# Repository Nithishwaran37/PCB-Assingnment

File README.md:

View this project on [CADLAB.io](https://cadlab.io/project/29285). 

# PCB-Assingnment

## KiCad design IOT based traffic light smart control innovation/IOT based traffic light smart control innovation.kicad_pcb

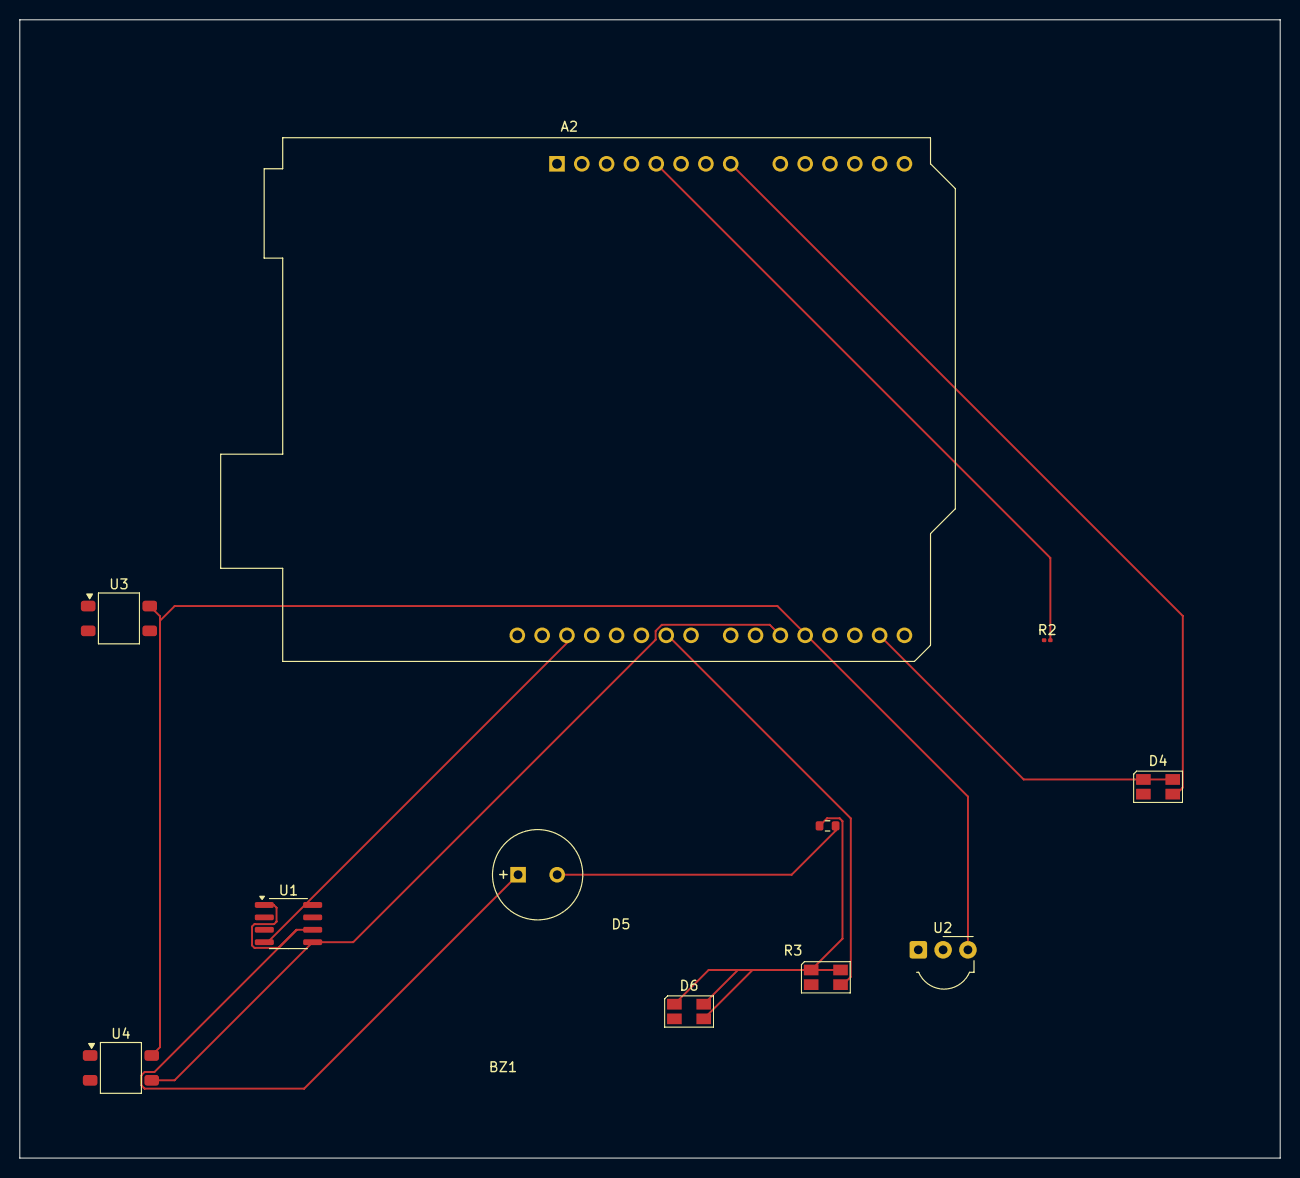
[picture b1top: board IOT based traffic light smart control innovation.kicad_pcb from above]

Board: 2 copper layers, 129.0 x 116.5 mm, 11 parts (0 on the bottom side), 10 nets.

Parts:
A2: Arduino_UNO_R2
BZ1: Buzzer; MagneticBuzzer_PUI_AT-0927-TT-6-R
D4, D5, D6: ASMB-MTB1-0A3A2; LED_Avago_PLCC4_3.2x2.8mm_CW
R2: R; R_0201_0603Metric
R3: R_Small_US; R_0603_1608Metric
U1: ESP-PSRAM32; SOIC-8_3.9x4.9mm_P1.27mm
U2: TSDP341xx; Vishay_MOLD-3Pin
U3, U4: IRM-H6xxT; Everlight_IRM-H6xxT

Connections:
Earth: BZ1.2 (-), R3.2
unnamed: A2.5 (+5V), R2.2
unnamed: A2.16 (D1/TX), D4.1 (RK), D4.2 (GK)
unnamed: A2.19 (D4), U2.3 (Vs), U3.4 (Vcc), U4.4 (Vcc)
unnamed: A2.20 (D5), U1.5 (SI/SIO), U4.3 (OUT)
unnamed: A2.24 (D9), D5.3 (BK)
unnamed: A2.28 (D13), U1.4 (VSS), U1.8 (VCC)
unnamed: A2.8 (VIN), D4.3 (BK)
unnamed: BZ1.1 (+), U1.1 (~CE), U1.6 (SCLK)
unnamed: D5.1 (RK), D5.2 (GK), D6.1 (RK), D6.2 (GK), D6.3 (BK), R3.1

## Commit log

2025-04-20 pcb assignment
2025-04-20 Backlink to CADLAB.io has been added.
